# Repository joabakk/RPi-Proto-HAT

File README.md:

# RPi-Proto-HAT
Prototyping Area HAT (Hardware Attached on Top) for Raspberry Pi Model A+ and B+.

Shop: 
[RPi-Proto-HAT](http://www.watterott.com/en/RPi-Proto-HAT) ([Amazon](http://www.amazon.de/RPi-Proto-HAT/dp/B00NBKXQPW)), 
[RPi-Proto-HAT with ID-EEPROM](http://www.watterott.com/en/RPi-Proto-HAT-ID-EEPROM)

## Features
* Prototyping Area
* ID EEPROM
* [Raspberry Pi HAT](https://github.com/raspberrypi/hats) compatible

## Hardware
* [Schematics + Layout](https://github.com/watterott/RPi-Proto-HAT/tree/master/pcb)

## Software
* [Flash/Update EEPROM](https://github.com/joabakk/RPi-Proto-HAT/blob/master/docu/EEPROM.md)

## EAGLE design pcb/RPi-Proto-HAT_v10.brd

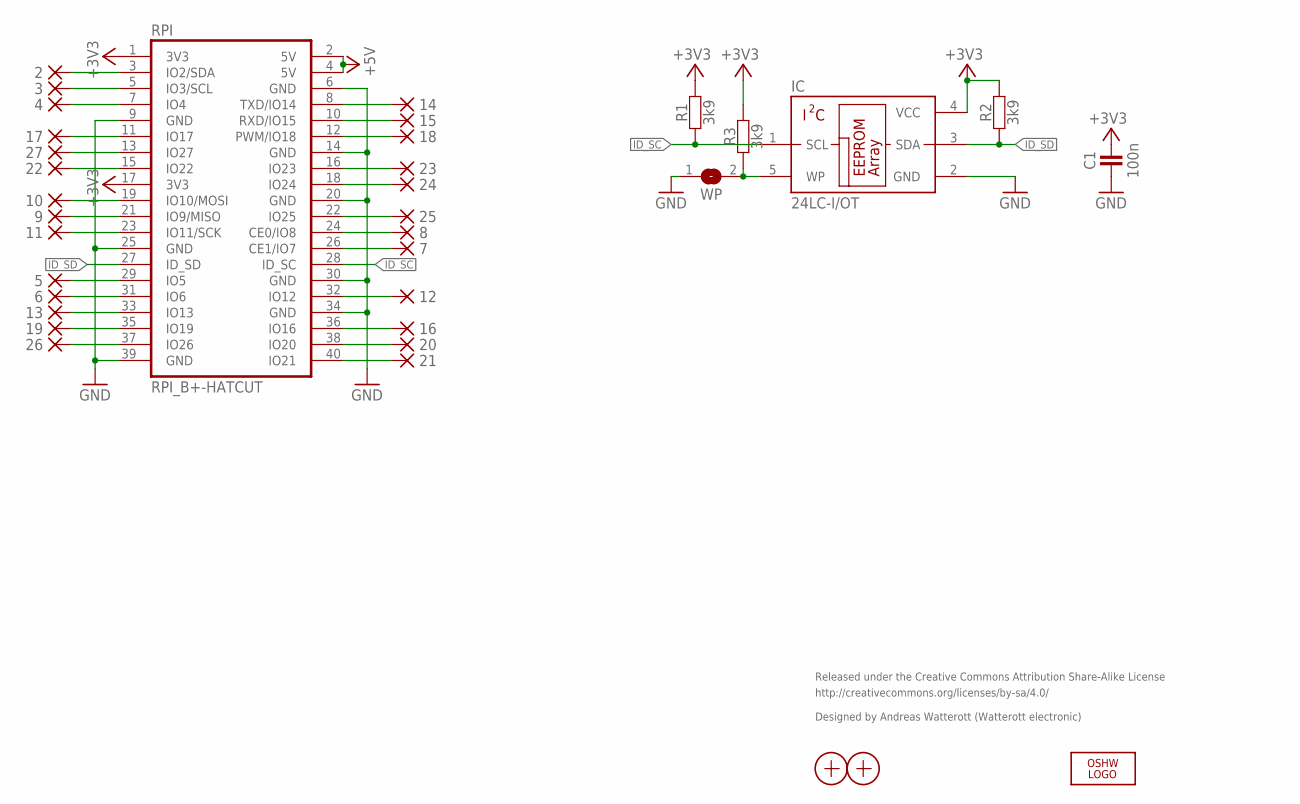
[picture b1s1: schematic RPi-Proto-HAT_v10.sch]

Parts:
2, 3, 4, 5, 6, 7, 8, 9, 10, 11, 12, 13, 14, 15, 16, 17, 18, 19, 20, 21, 22, 23, 24, 25, 26, 27: PAD-1-1.6
C1: 100n; R0603
IC: 24LC-I/OT; SOT23-5
LOGO2: OSHW_LOGOX0070; OSHW_6X70
R1, R2, R3: 3k9; R0603
RPI: RPI_B+-HATCUT; RPI-B+HAT_CUTOUT
WP: JUMPER2-NOCREAM; JUMPER2_NC
X1, X2: PASSER-07; PASSER_07MM

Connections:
+3V3: C1.2, IC.4 (VCC), R1.2, R2.2, R3.2, RPI.1 (3V3), RPI.17 (3V3)
+5V: RPI.2 (5V), RPI.4 (5V)
GND: C1.1, IC.2 (GND), RPI.6 (GND), RPI.9 (GND), RPI.14 (GND), RPI.20 (GND), RPI.25 (GND), RPI.30 (GND), RPI.34 (GND), RPI.39 (GND), WP.1
ID_SC: IC.1 (SCL), R1.1, RPI.28 (ID_SC)
ID_SD: IC.3 (SDA), R2.1, RPI.27 (ID_SD)
IO2: 2.1, RPI.3 (IO2/SDA)
IO3: 3.1, RPI.5 (IO3/SCL)
IO4: 4.1, RPI.7 (IO4)
IO5: 5.1, RPI.29 (IO5)
IO6: 6.1, RPI.31 (IO6)
IO7: 7.1, RPI.26 (CE1/IO7)
IO8: 8.1, RPI.24 (CE0/IO8)
IO9: 9.1, RPI.21 (IO9/MISO)
IO10: 10.1, RPI.19 (IO10/MOSI)
IO11: 11.1, RPI.23 (IO11/SCK)
IO12: 12.1, RPI.32 (IO12)
IO13: 13.1, RPI.33 (IO13)
IO14: 14.1, RPI.8 (TXD/IO14)
IO15: 15.1, RPI.10 (RXD/IO15)
IO16: 16.1, RPI.36 (IO16)
IO17: 17.1, RPI.11 (IO17)
IO18: 18.1, RPI.12 (PWM/IO18)
IO19: 19.1, RPI.35 (IO19)
IO20: 20.1, RPI.38 (IO20)
IO21: 21.1, RPI.40 (IO21)
IO22: 22.1, RPI.15 (IO22)
IO23: 23.1, RPI.16 (IO23)
IO24: 24.1, RPI.18 (IO24)
IO25: 25.1, RPI.22 (IO25)
IO26: 26.1, RPI.37 (IO26)
IO27: 27.1, RPI.13 (IO27)
WP: IC.5 (WP), R3.1, WP.2

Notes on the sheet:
Released under the Creative Commons Attribution Share-Alike License
http://creativecommons.org/licenses/by-sa/4.0/
Designed by Andreas Watterott (Watterott electronic)

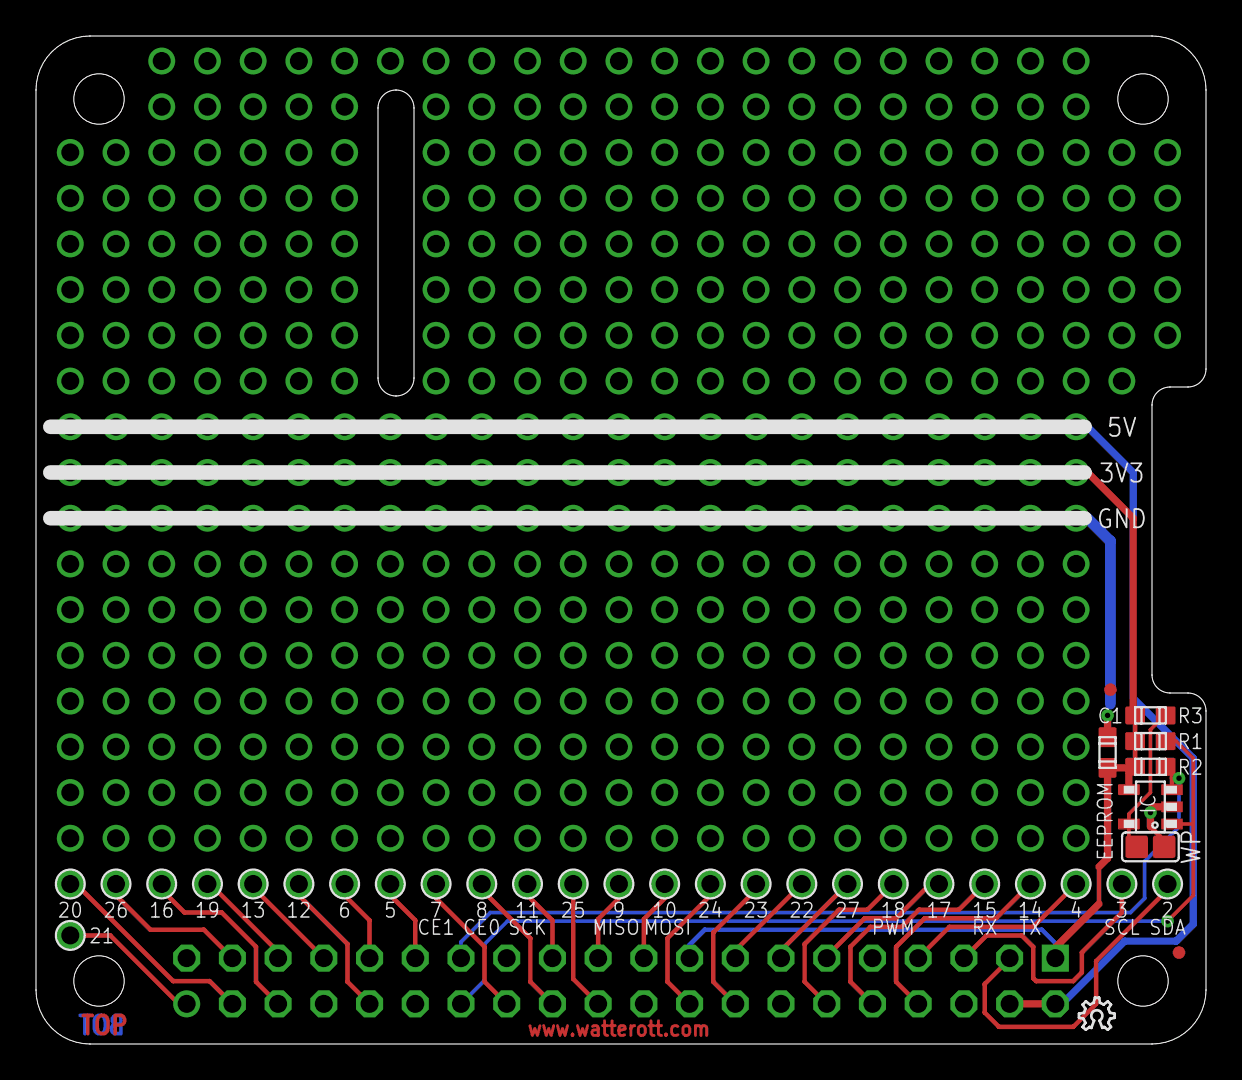
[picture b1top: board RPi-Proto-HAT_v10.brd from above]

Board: 2 copper layers, 65.0 x 56.0 mm, 36 parts (0 on the bottom side), 32 nets.

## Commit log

2014-08-15 added readme
2014-09-04 added layout and schematics
2014-09-04 added image
2014-11-06 cleaned up schematics and layout
2014-11-06 added EEPROM data
2015-01-11 moved image
2015-01-17 Update README.md
    changed software link
2015-01-17 Update rpi-proto-hat.txt
    pin27 pulled high, vendor name and description changed
2015-01-17 Update EEPROM.md
    eeprom data link changed
2015-01-18 Update rpi-proto-hat.txt
    uuid removed
2015-01-19 Update rpi-proto-hat.txt
    Comment on p27 pull-up
